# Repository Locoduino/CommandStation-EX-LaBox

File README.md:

# What is Labox ?

Labox is a projet to build a small DCC Command Station with a dedicated hardware based on ESP32.
The goal is to be able to drive DCC machines, but also use Railcom standard and CAN bus connectivity.
You can find more information on [Locoduino website](https://locoduino.org/).
The software is based on DCC-EX CommandStation software (see below...).

# How to start implementing Labox ?

* Open the file ``CommandStation-EX-LaBox.ino`` in the Arduino IDE or Visual Studio Code (VSC) with PlatformIO extension. Please do not rename the folder containing the sketch code, nor add any files in that folder. The Arduino IDE relies on the structure and name of the folder to properly display and compile the code. 
* Rename or copy ``config.Labox.h`` to ``config.h``. 
* You must edit ``config.h`` according to the help texts in ``config.h``.

# Hardware

Labox is based on a specific PCB designed by Locoduino. The design and gerber files can be found in the 'PCB' folder.

# More information
You can learn more at the [Locoduino website](https://locoduino.org/)

# What is DCC-EX?
DCC-EX is a team of dedicated enthusiasts producing open source DCC & DC solutions for you to run your complete model railroad layout. Our easy to use, do-it-yourself, and free open source products run on off-the-shelf Arduino technology and are supported by numerous third party hardware and apps like JMRI, Engine Driver, wiThrottle, Rocrail and more. 

Currently, our products include the following:

* [EX-CommandStation](https://github.com/DCC-EX/CommandStation-EX/releases)
* [EX-WebThrottle](https://github.com/DCC-EX/exWebThrottle)
* [EX-Installer](https://github.com/DCC-EX/EX-Installer)
* [EX-MotoShield8874](https://dcc-ex.com/reference/hardware/motorboards/ex-motor-shield-8874.html#gsc.tab=0)
* [EX-DCCInspector](https://github.com/DCC-EX/DCCInspector-EX)
* [EX-Toolbox](https://github.com/DCC-EX/EX-Toolbox)
* [EX-Turntable](https://github.com/DCC-EX/EX-Turntable)
* [EX-IOExpander](https://github.com/DCC-EX/EX-IOExpander)
* [EX-FastClock](https://github.com/DCC-EX/EX-FastClock)
* [DCCEXProtocol](https://github.com/DCC-EX/DCCEXProtocol)

Details of these projects can be found on [our web site](https://dcc-ex.com/).

# What’s in this Repository?

This repository, CommandStation-EX, contains a complete DCC-EX *EX-CommmandStation* sketch designed for compiling and uploading into an Arduino Uno, Mega, or Nano.

To utilize this sketch, you can use the following: 

1. (recommended for all levels of user) our [automated installer](https://github.com/DCC-EX/EX-Installer)
2. (intermediate) download the latest version from the [releases page](https://github.com/DCC-EX/CommandStation-EX/releases)
3. (advanced) use git clone on this repository 

Refer to [our web site](https://https://dcc-ex.com/ex-commandstation/get-started/index.html#/) for the hardware required for this project.

**We seriously recommend using the EX-Installer**, however if you choose not to use the installer... 

* Open the file ``CommandStation-EX.ino`` in the Arduino IDE or Visual Studio Code (VSC). Please do not rename the folder containing the sketch code, nor add any files in that folder. The Arduino IDE relies on the structure and name of the folder to properly display and compile the code. 
* Rename or copy ``config.example.h`` to ``config.h``. 
* You must edit ``config.h`` according to the help texts in ``config.h``.

# More information
You can learn more at the [DCC-EX website](https://dcc-ex.com/)

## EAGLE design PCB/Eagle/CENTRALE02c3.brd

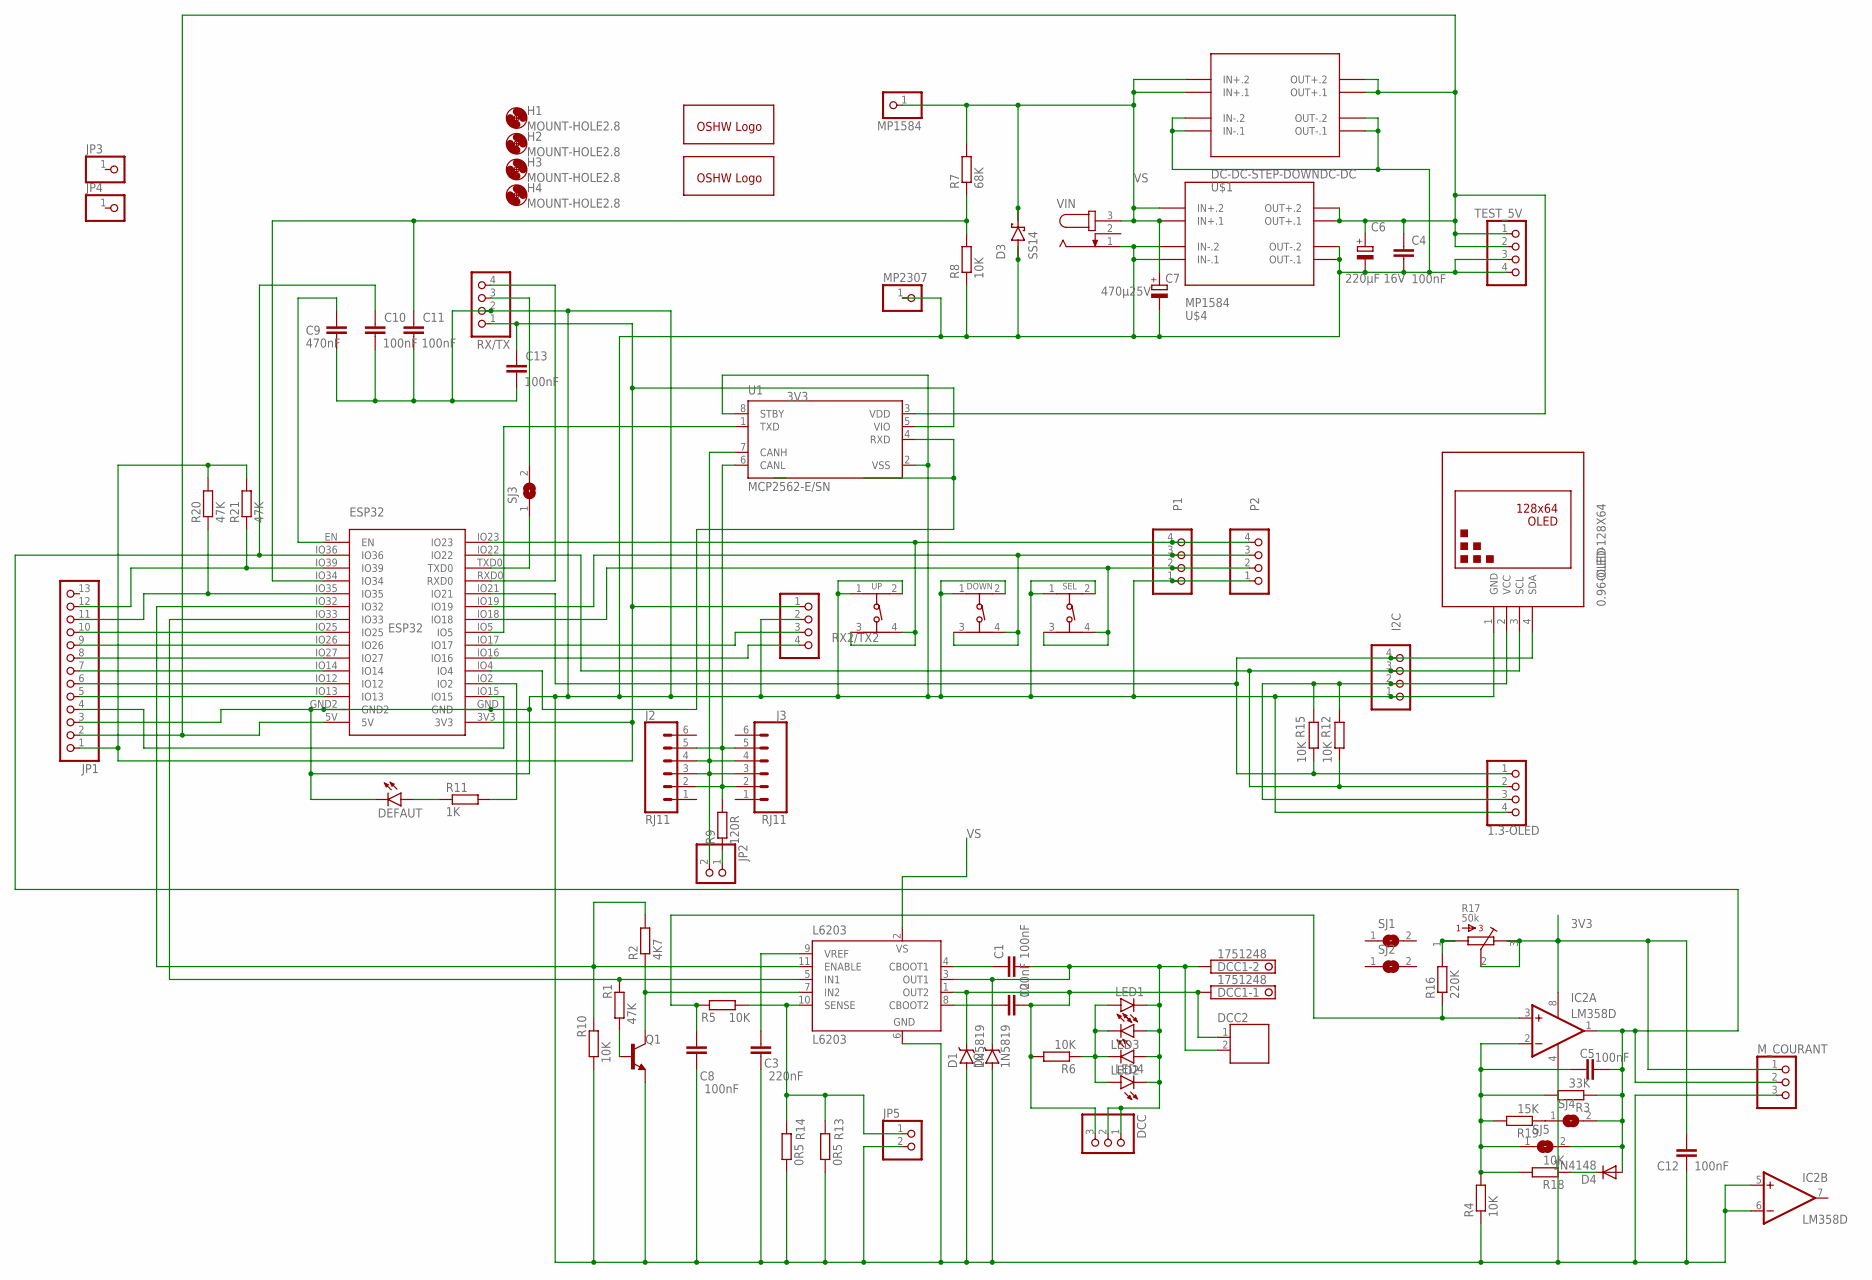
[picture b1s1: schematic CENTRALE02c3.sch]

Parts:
0.96-OLED: OLED-128X64; DISPLAY-OLED-128X64-I2C
1.3-OLED: PINHD-1X4; 1X04
C1, C2, C4, C5, C8, C10, C11, C12, C13: 100nF; C1206
C3: 220nF; C1206
C6: 220µF 16V; E2,5-7
C7: 470µ25V; E5-10,5
C9: 470nF; C1206
D1, D2: 1N5819; SMA-DIODE
D3: SS14; DIOM4325X250N
D4: 1N4148; DO35-7
DCC: PINHD-1X3; 1X03
DCC1: 1751248
DCC2: 691502710002
DEFAUT: LEDSMT1206; 1206
DOWN: 430456073736; 4304X60737X6
ESP32: ESP32
GOLD_ORB_SM1, GOLD_ORB_SM2: OSHWLOGOLOGO5MM; OSHW_5MM
H1, H2, H3, H4: MOUNT-HOLE2.8; 2,8
I2C: PINHD-1X4; 1X04
IC2: LM358D; SO08
J2, J3: RJ11; RJ11-6
JP1: PINHD-1X13; 1X13
JP2, JP5: PINHD-1X2; 1X02
JP3, JP4: PINHD-1X1; 1X01
L6203: L6203; MULTIWATT-11
LED1, LED3: LEDSMT1206; 1206
LED2, LED4: LED3MM
MP1584, MP2307: PINHD-1X1; 1X01
M_COURANT: PINHD-1X3; 1X03
P1, P2: PINHD-1X4; 1X04
Q1: MMBT3904LT1-NPN-SOT23-BEC; SOT23-BEC
R1, R20, R21: 47K; R0805
R2: 4K7; R0805
R3: 33K; R0805
R4, R5, R6, R8, R10, R12, R15, R18: 10K; R0805
R7: 68K; R0805
R9: 120R; M1206
R11: 1K; R0805
R13, R14: 0R5; R2512
R16: 220K; R0805
R17: 50k; 3386-MULTI
R19: 15K; R0805
RX2/TX2: PINHD-1X4; 1X04
RX/TX: PINHD-1X4; 1X04
SEL: 430456073736; 4304X60737X6
SJ1, SJ2, SJ3, SJ4, SJ5: SJ
TEST_5V: PINHD-1X4; 1X04
U1: MCP2562-E/SN; SOIC127P600X175-8N
U$1: DC-DC-STEP-DOWNDC-DC; DC-DC-STEP-DOWN
U$4: MP1584; DC-DC-STEP-DOWN-MP1584
UP: 430456073736; 4304X60737X6
VIN: JACK-PLUG0; SPC4077

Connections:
3V3: 0.96-OLED.2 (VCC), 1.3-OLED.3, C12.2, C13.2, ESP32.3V3, I2C.2, IC2.8 (V+), JP1.1, M_COURANT.1, R12.1, R15.1, R17.2, R17.3, R17.6, R20.2, R21.2, RX2/TX2.1, RX/TX.1, U1.5 (VIO)
GND: 0.96-OLED.1 (GND), 1.3-OLED.4, C3.1, C4.2, C6.-, C7.-, C8.1, C9.2, C10.1, C11.1, C12.1, C13.1, D1.A, D2.A, D3.A, DEFAUT.C, DOWN.1, DOWN.2 (3), ESP32.GND, ESP32.GND2, I2C.1, IC2.4 (V-), IC2.5 (+IN), IC2.6 (-IN), JP1.3, JP5.2, L6203.6 (GND), MP2307.1, M_COURANT.3, P1.1, P2.1, Q1.E, R4.1, R8.1, R10.1, R13.1, R14.1, RX2/TX2.2, RX/TX.2, SEL.1, SEL.2 (3), TEST_5V.3, TEST_5V.4, U1.2 (VSS), U1.8 (STBY), U$1.IN-.1, U$1.IN-.2, U$1.OUT-.1, U$1.OUT-.2, U$4.IN-.1, U$4.IN-.2, U$4.OUT-.1, U$4.OUT-.2, UP.1, UP.2 (3), VIN.1
unnamed: L6203.7 (IN2), Q1.C, R2.1
unnamed: C1.1, L6203.4 (CBOOT1)
unnamed: C2.1, L6203.8 (CBOOT2)
unnamed: ESP32.IO15, JP1.4
unnamed: C2.2, D1.C, DCC.3, DCC1.1, DCC2.1, L6203.1 (OUT2), R6.2
unnamed: C1.2, D2.C, DCC.1, DCC.2, DCC1.2, DCC2.2, L6203.3 (OUT1), LED1.C, LED2.A, LED3.A, LED4.K (C)
unnamed: Q1.B, R1.1
unnamed: C5.1, IC2.2 (-IN), R3.2, R4.2, R18.2, R19.2, SJ5.1
unnamed: C3.2, L6203.9 (VREF)
unnamed: C5.2, C10.2, D4.A, ESP32.IO36, IC2.1 (OUT), M_COURANT.2, R3.1, SJ4.2, SJ5.2
unnamed: JP5.1, L6203.10 (SENSE), R5.1, R13.2, R14.2
unnamed: RX/TX.3, SJ3.2
unnamed: C11.2, ESP32.IO34, R7.1, R8.2
unnamed: C4.1, C6.+, ESP32.5V, JP1.2, TEST_5V.1, TEST_5V.2, U1.3 (VDD), U$1.OUT+.1, U$1.OUT+.2, U$4.OUT+.1, U$4.OUT+.2
unnamed: C8.2, IC2.3 (+IN), R5.2, R16.1
unnamed: J2.3, J2.4, J3.3, J3.4, JP2.2, U1.7 (CANH)
unnamed: ESP32.IO5, U1.1 (TXD)
unnamed: ESP32.IO32, L6203.11 (ENABLE), R2.2, R10.2
unnamed: DEFAUT.A, R11.1
unnamed: ESP32.IO13, JP1.5
unnamed: ESP32.IO4, U1.4 (RXD)
unnamed: JP2.1, R9.1
unnamed: ESP32.IO12, JP1.6
unnamed: ESP32.IO23, P1.4, P2.4, UP.3 (2), UP.4
unnamed: ESP32.IO14, JP1.7
unnamed: ESP32.IO27, JP1.8
unnamed: ESP32.IO18, P1.2, P2.2, SEL.3 (2), SEL.4
unnamed: ESP32.IO26, JP1.9
unnamed: ESP32.IO35, JP1.11, R20.1
unnamed: ESP32.IO39, JP1.12, R21.1
unnamed: 0.96-OLED.4 (SDA), 1.3-OLED.1, ESP32.IO21, I2C.4, R15.2
unnamed: ESP32.IO25, JP1.10
unnamed: 0.96-OLED.3 (SCL), 1.3-OLED.2, ESP32.IO22, I2C.3, R12.2
unnamed: ESP32.IO33, L6203.5 (IN1), R1.2
unnamed: R16.2, R17.1, R17.4
unnamed: ESP32.IO17, RX2/TX2.3
unnamed: D4.C, R18.1
unnamed: LED1.A, LED2.K (C), LED3.C, LED4.A, R6.1
unnamed: R19.1, SJ4.1
unnamed: DOWN.3 (2), DOWN.4, ESP32.IO19, P1.3, P2.3
unnamed: J2.2, J2.5, J3.2, J3.5, R9.2, U1.6 (CANL)
unnamed: ESP32.RXD0, RX/TX.4
unnamed: ESP32.TXD0, SJ3.1
unnamed: ESP32.IO2, R11.2
unnamed: C9.1, ESP32.EN
unnamed: ESP32.IO16, RX2/TX2.4
VS: C7.+, D3.C (K), L6203.2 (VS), MP1584.1, R7.2, U$1.IN+.1, U$1.IN+.2, U$4.IN+.1, U$4.IN+.2, VIN.3

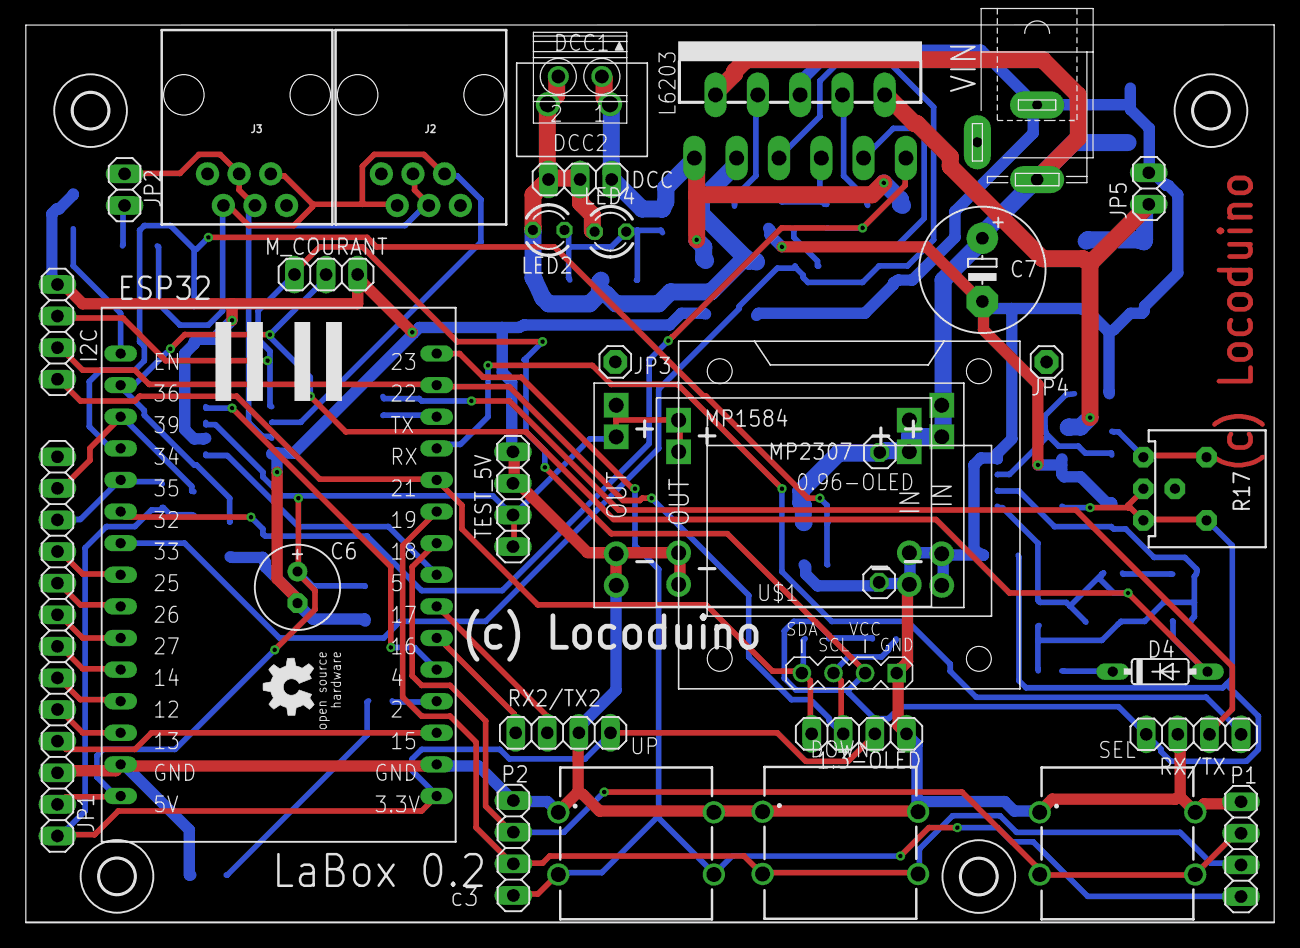
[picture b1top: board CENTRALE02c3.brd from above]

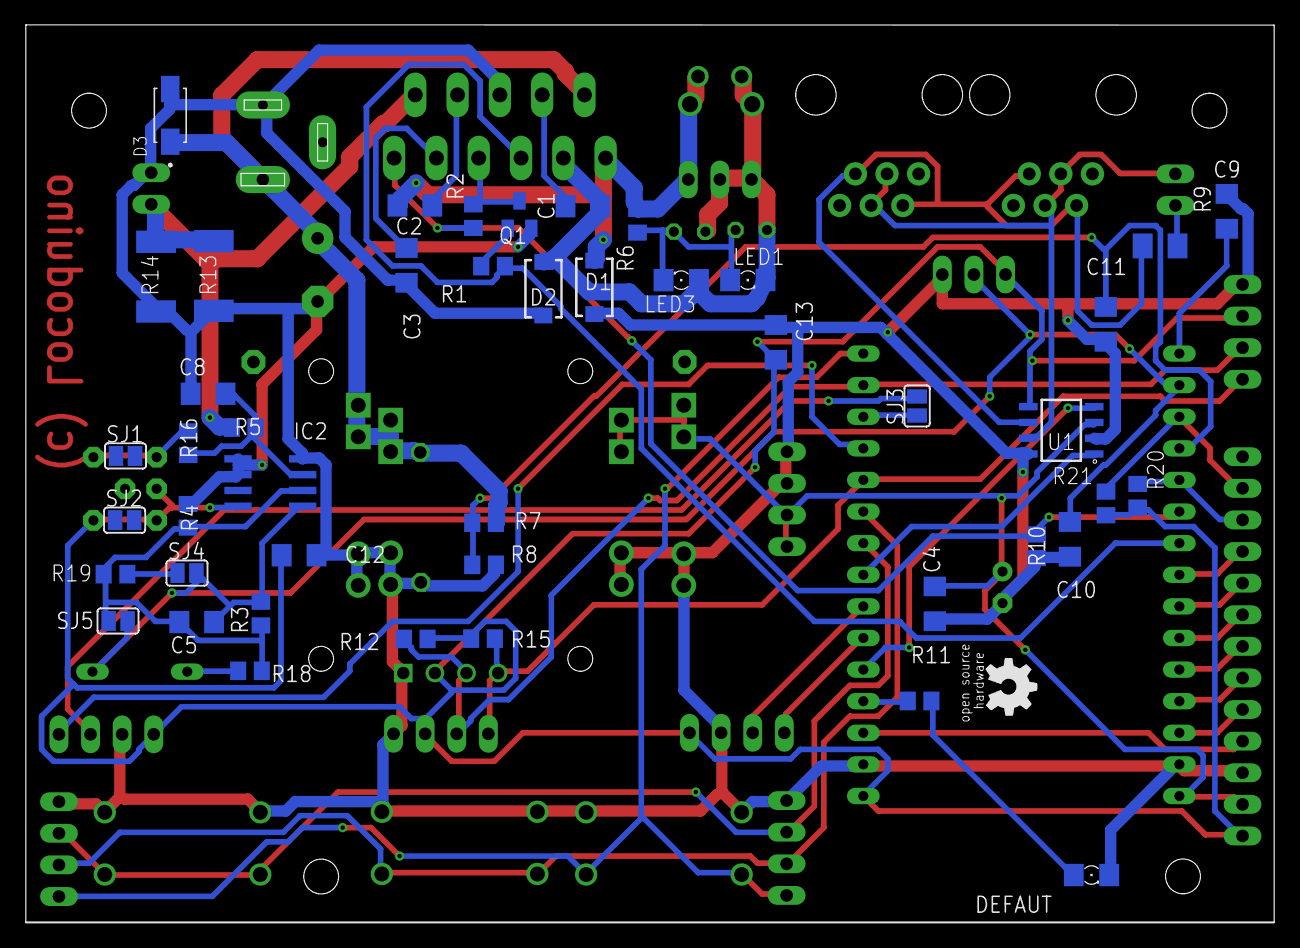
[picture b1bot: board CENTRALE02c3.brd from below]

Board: 2 copper layers, 100.3 x 72.1 mm, 86 parts (46 on the bottom side), 49 nets.

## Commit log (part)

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2022-10-16 First version with DCC output + HMI
2022-11-15 First functionnal version
2022-11-15 First functionnal version 2
2022-11-17 Update README.md
    Change Readme...
2022-11-18 WIfi AP mode working
2023-04-18 First Z21 version
2023-04-22 Working Z21
2023-04-22 Version
2023-05-04 2.2.0 Read CV works !
2023-05-05 Formatting + Auto power On at start for Z21
2023-05-18 2.2.1 Read/Write any CV in prog mode
2023-09-17 2.2.2 Improvements for CV reading
2023-09-20 Base config for Labox.
2023-09-21 Revert "Merge branch 'master' into LaBox"
    This reverts commit 44e6ac6541511a0d5c3dabf24f10aa90de060617, reversing
    changes made to bb87541400e85b9f4c4ef50f9ecfd289e5df2a42.
2023-10-17 CommandStation 5.0 2.2.2
2023-10-21 Fix compil pb
2023-10-21 Fix compil pb 2
2023-10-21 main.yml
2023-10-22 Misc
2023-10-23 Improve UI
2023-10-24 Fix LABOX_PROG_MOTOR_SHIELD
2023-11-07 Fix basic config
2023-11-21 #define HMI_SHOW_CURRENT...
2023-12-01 2.4.0
2023-12-05 deltaCurrent
2023-12-07 Fix USE_HMI
2023-12-07 2.4.1
2023-12-09 Ajout de fonctions pour retour message
2023-12-09 Fix oubli break ligne 78
2023-12-10 Add POWERMODE::OVERLOAD
2024-02-10 2.4.2
2024-02-11 2.4.3
2024-02-18 2.4.4
2024-02-24 2.4.5
2024-02-25 2.4.5 Part II
2024-02-25 2.4.5 Part III
2024-02-25 2.4.5 Fix platforim.IO
2024-03-09 2.4.6
2024-03-10 2.4.7
2024-03-23 LaBox 2.4.7
2024-03-29 Mise en conformité sources.
2024-03-29 0.6.4
2024-08-09 Railcom from lebelge
2024-08-10 2.4.8 Merge with EX master...
2024-08-11 2.5.1
2024-08-11 2.5.1 Part II
2024-08-22 2.4.9
2024-08-22 2.5.2
2024-08-22 2.5.2 II
2024-08-23 2.5.2 III
2024-09-07 2.6.2
2024-09-07 2.6.2 II
2024-09-08 2.6.3
2024-09-08 2.6.3 II
2024-09-08 2.6.3 III
2024-09-14 2.6.4
2024-09-14 2.6.4 II
2024-09-17 2.6.5
2024-09-17 2.6.5 II
2024-09-23 2.6.6
2024-10-08 2.7.0
2024-10-19 2.8.0
2024-10-19 2.8.0 II
2024-10-20 2.8.0 III
2024-11-16 2.9.0
2024-11-16 2.9.0 II
2024-11-16 2.9.0 III
2024-11-24 PCB c3
2025-01-31 PCB 03c4
2025-01-31 2.9.1
2025-01-31 2.9.1 Part II
2025-01-31 PCB 0.3c4 II
2025-05-17 2.10.0
2025-05-17 2.10.0 II
2025-05-18 2.10.0 PCB production files
2025-05-20 2.10.0 PCB Production files II
2025-05-20 2.10.0 III
2025-05-30 PCB 1.0a2
2025-06-15 PCB 1.0a3
2025-06-28 PCB 1.0a4
2025-07-11 PCB 1.0a4 II
2025-07-20 PCB 1.0a5 II
2025-07-20 PCB 1.0a5 III
2025-08-09 PCB 1.0 b0
2025-08-11 PCB 1.00 b0 II
2025-08-25 2.4.11.0
2025-08-25 2.4.11.0 II
2025-10-03 PCB 1.0b1
2025-11-08 PCB 1.0b1 II
2025-11-11 PCB 1.0b1 III
2025-11-21 2.4.12.0
2025-11-21 2.4.12.0 II
2025-11-21 2.4.12.0 III
2025-12-09 2.13.0
2026-03-31 2.14.0
2026-03-31 2.14 II
2026-03-31 2.14.0 III
2026-03-31 2.14.0 IV
2026-04-06 2.15.0
2026-05-24 Remove config.h

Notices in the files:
parts and their libraries:
diy-modules: Released under the Creative Commons Attribution 4.0 International License: http://creativecommons.org/licenses/by/4.0
SparkFun-Connectors: Licensing: Creative Commons ShareAlike 4.0 International - https://creativecommons.org/licenses/by-sa/4.0
